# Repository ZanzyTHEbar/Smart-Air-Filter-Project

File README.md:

# :man_technologist:

## Smart Air Filter Project Controller

## :cat: Air Filter Project for Cats and Home :cat2:

This repo is dedicated to the **Smart Air Filter Project**, an automated system for purifying cat litter air.

# WHAT IS THIS PROJECT

This project is dedicated to designing PCB and programming files to bring Smart Air Filtering to the DIY community. Using water as the filtration medium, no need for expensive consumable filters. 

# Things to Do

**__Hardware__**

- [x] Formulate project as PlatformIO
- [x] Integrate the PCB schematic layout
- [x] Integrate a BOM parts list for PCB
- [x] Integrate a Pick and Place file
- [ ] Integrate Panelised PCB gerber files
- [ ] Integrate SPI SRAM chip instead of SD Card
- [ ] Integrate speakers for audio feedback

**__Software__**

- [x] Implement proper memory management
- [ ] Implement proper error handling&logging
- [ ] Implement proper documentation
- [ ] Implement proper debugging for testing
- [ ] Add custom sounds for speakers
- [x] implement code as proper custom library
- [ ] implement dual core system archtecture
        --> Networking on one core and Application code on the other (esp32 is dual core)

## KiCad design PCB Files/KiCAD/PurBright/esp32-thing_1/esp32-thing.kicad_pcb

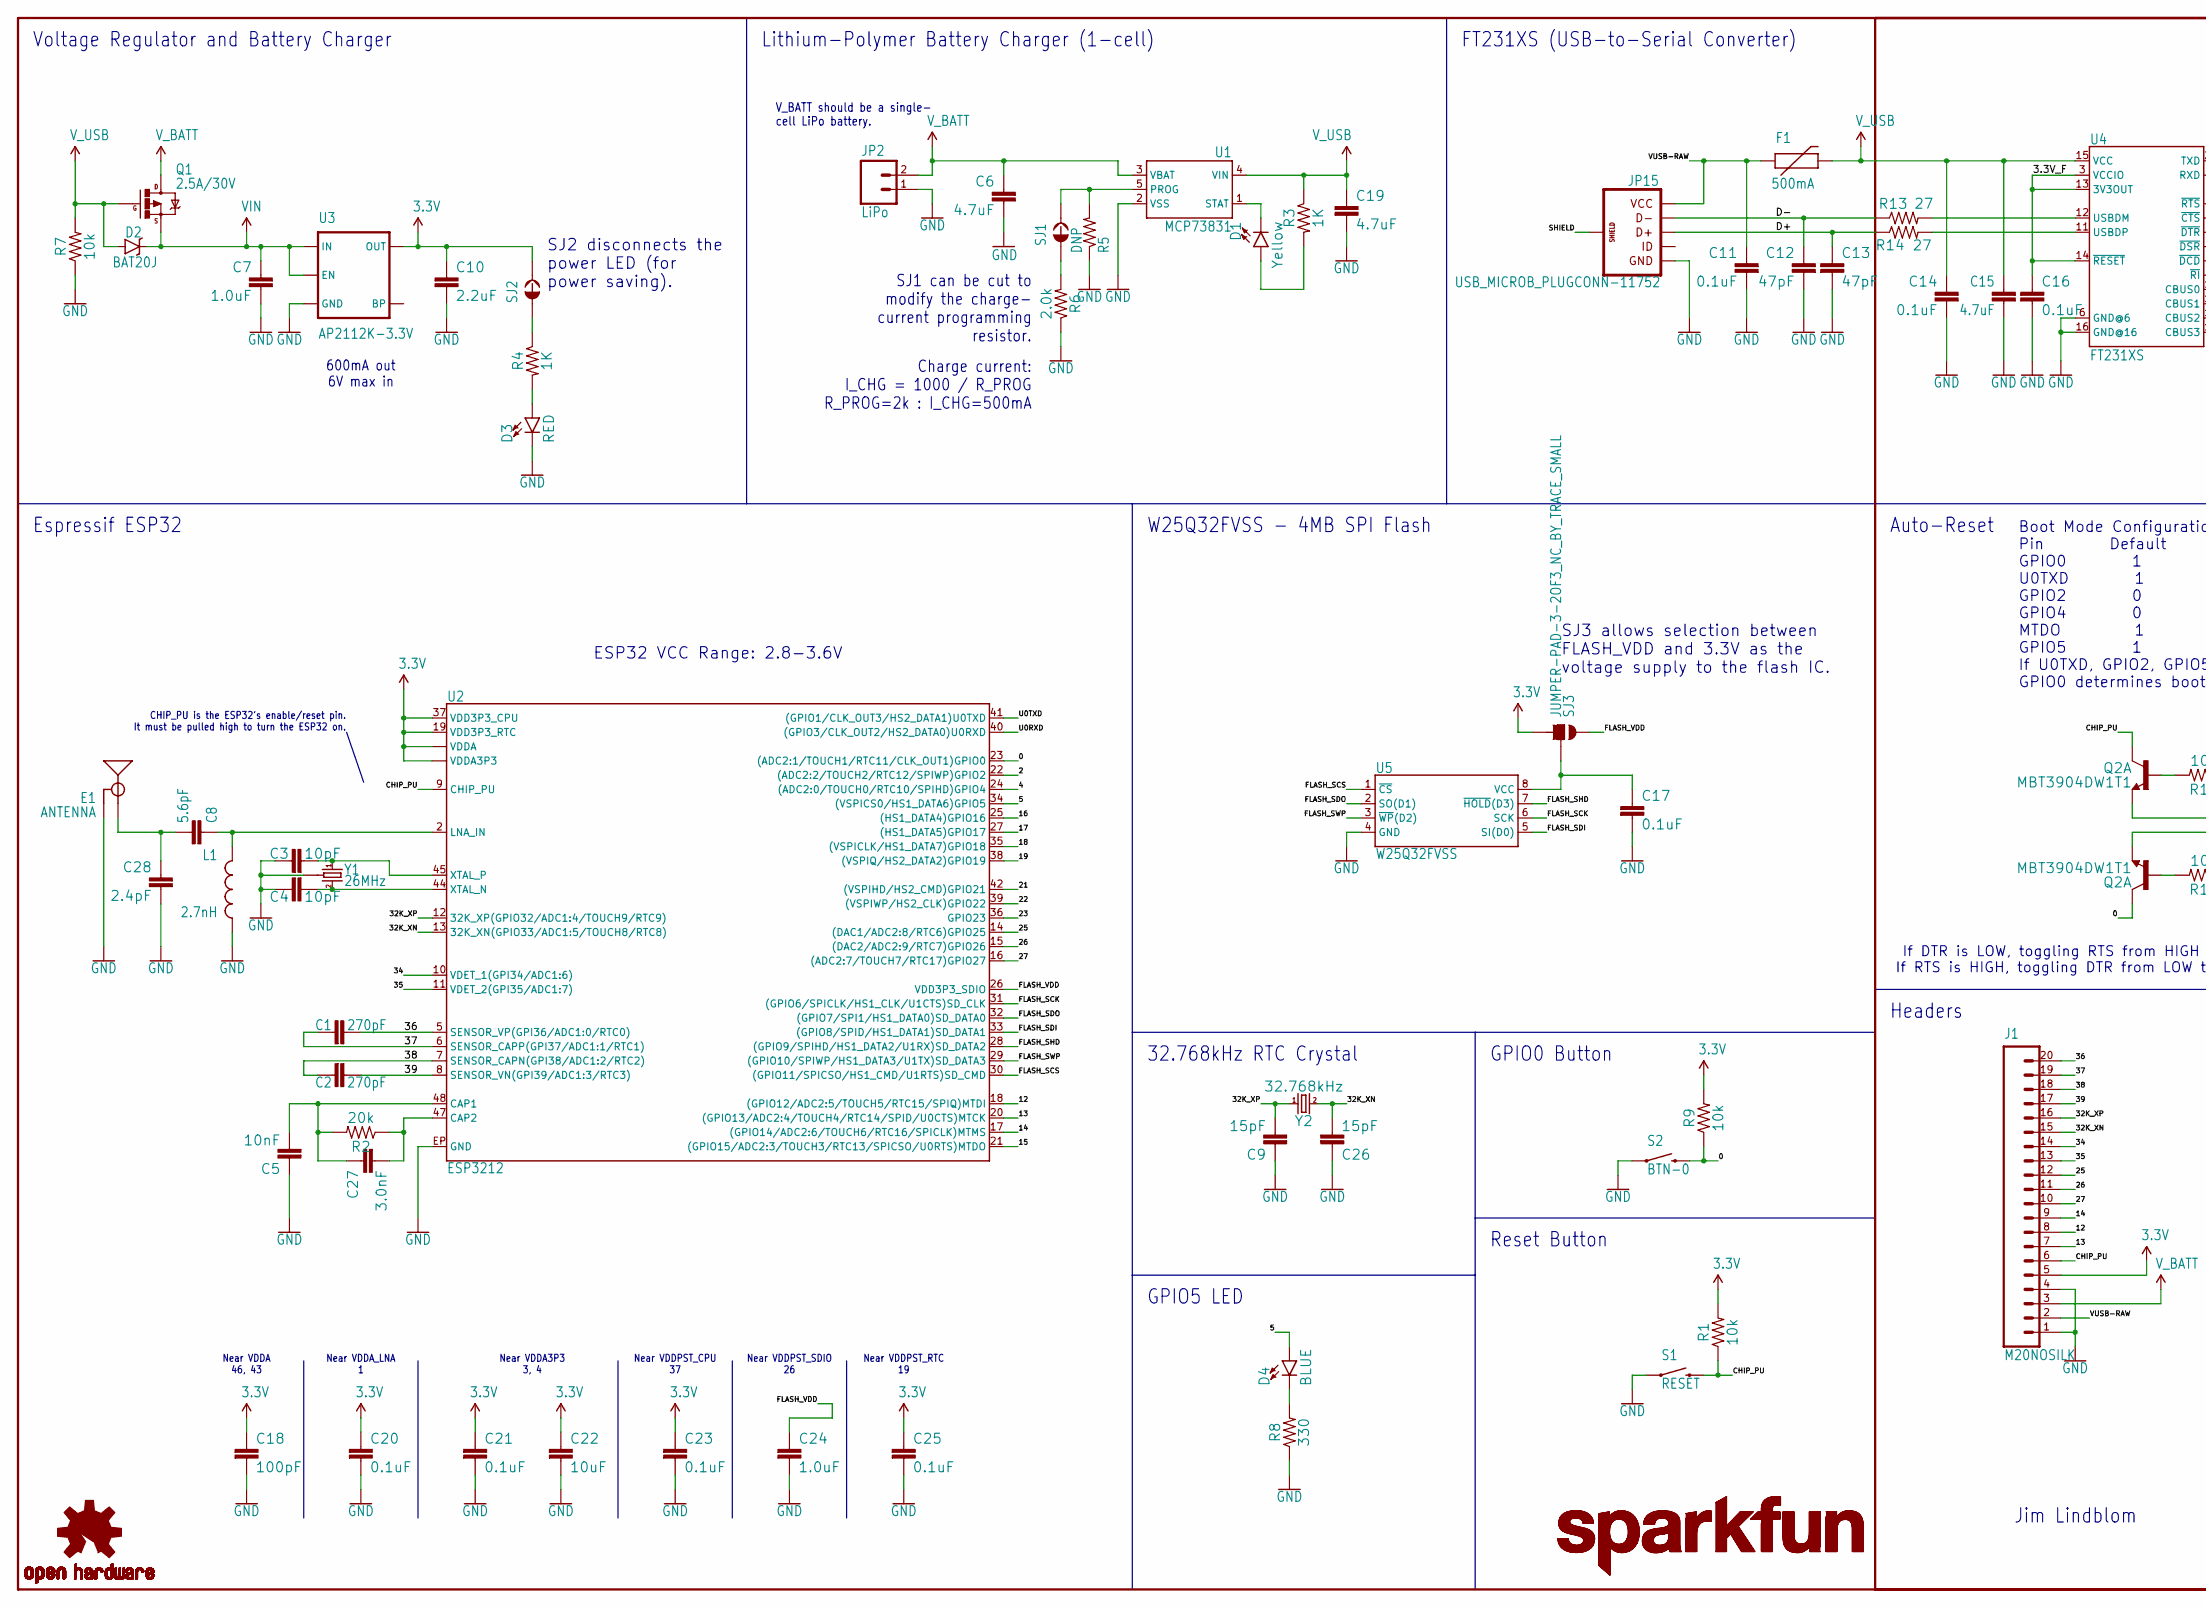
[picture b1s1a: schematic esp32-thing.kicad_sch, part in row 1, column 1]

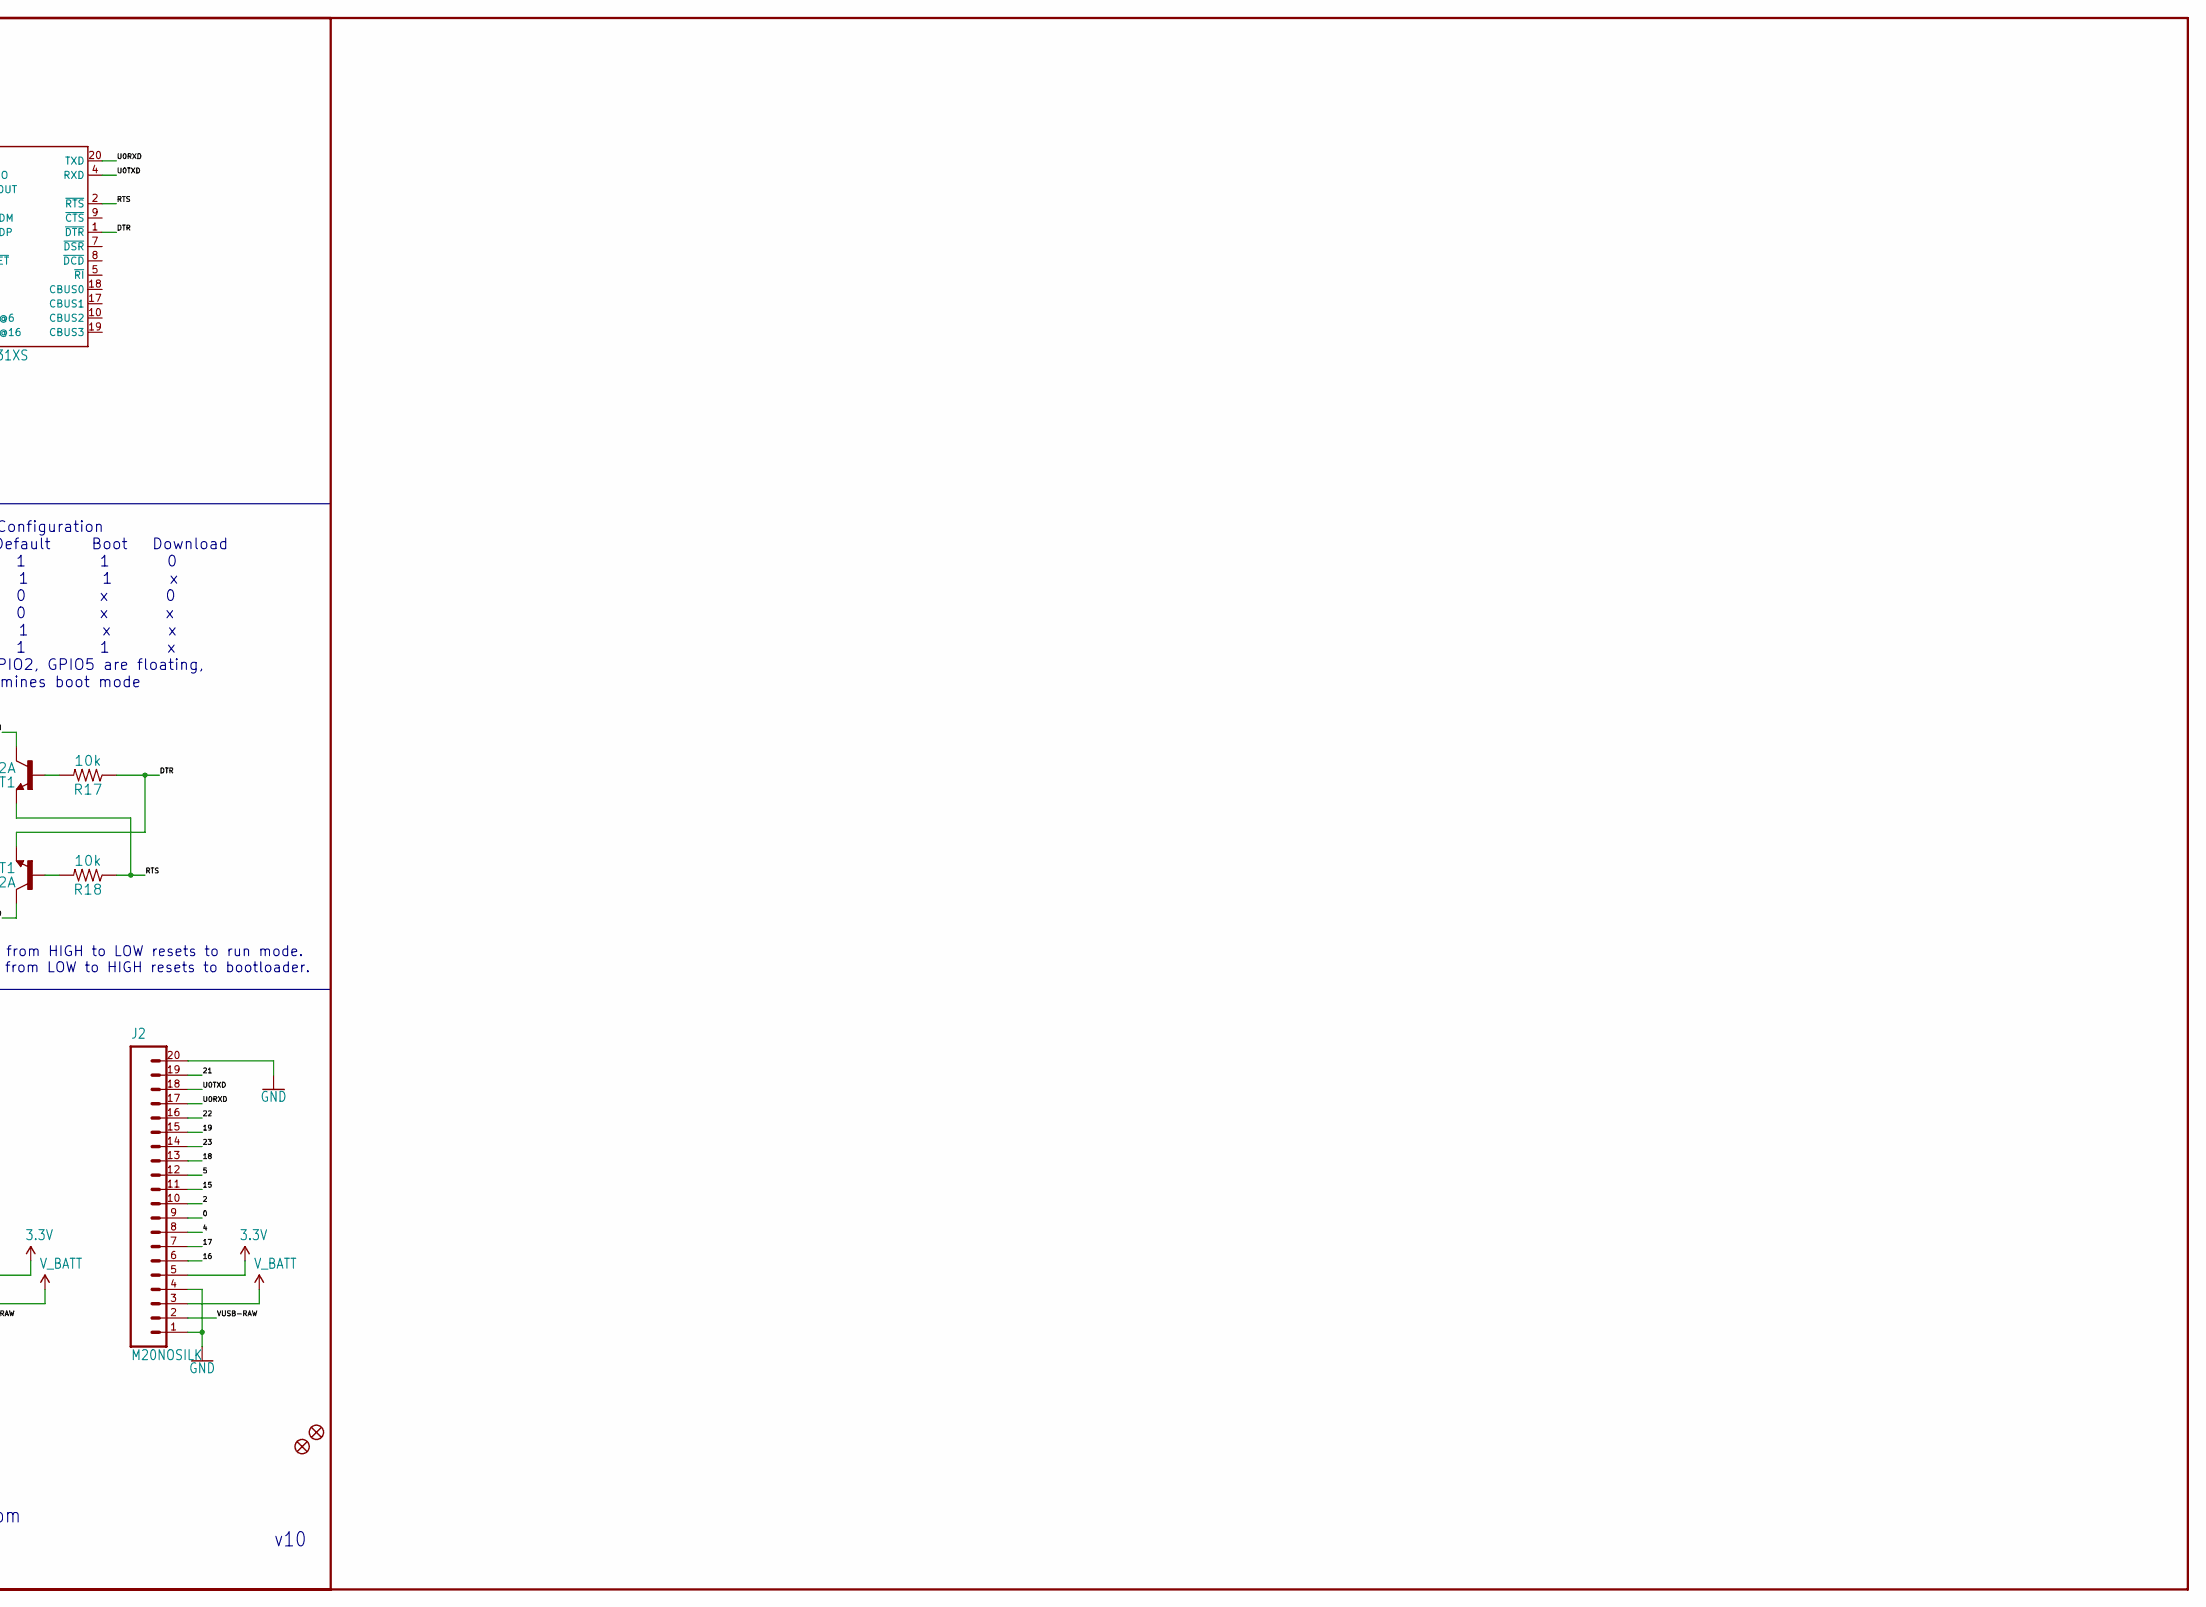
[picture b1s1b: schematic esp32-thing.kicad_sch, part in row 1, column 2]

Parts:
C1, C2: 270pF; 0603
C3, C4: 10pF; 0603
C5: 10nF; 0603
C6, C19: 4.7uF; 0603
C7: 1.0uF; 0805
C8: CAP-12456; 0603
C9, C26: 15pF; 0603
C10: 2.2uF; 0603
C11, C14, C16, C17, C20, C21, C23, C25: 0.1uF; 0603
C12, C13: 47pF; 0603
C15: 4.7uF; 0603-CAP
C18: 100pF; 0603
C22: 10uF; 0603
C24: 1.0uF; 0603
C27: 3.0nF; 0603
C28: 2.4pF; 0603
D1: Yellow; LED-0603
D2: BAT20J; SOD-323
D3: RED; LED-0603
D4: BLUE; LED-0603
E1: ANTENNA; TRACE_ANTENNA_2.4GHZ_25.7MM_TUNED
F1: 500mA; PTC-1206
FD1, FD2: FIDUCIALUFIDUCIAL; MICRO-FIDUCIAL
FRAME1: FRAME-LEDGER; CREATIVE_COMMONS
J1, J2: M20NOSILK; 1X20_NOSILK
JP2: LiPo; JST-2-PTH
JP15: USB_MICROB_PLUGCONN-11752; USB-B-MICRO-SMD_V03
L1: NDUC-08762; 0603
LOGO1, LOGO3: SFE_LOGO_NAME.2_INCH; SFE_LOGO_NAME_.2
LOGO2: OSHW-LOGOMINI; OSHW-LOGO-MINI
Q1: 2.5A/30V; SOT23-3
Q2: MBT3904DW1T1; SC70-6
R1, R7, R9, R17, R18: 10k; 0603
R2: 20k; 0603
R3, R4: 1K; 0603
R5: DNP; 1_6W-RES
R6: 2.0k; 0603
R8: 330; 0603
R13, R14: 27; 0603
S1: RESET; TACTILE_SWITCH_SMD_4.6X2.8MM
S2: BTN-0; TACTILE_SWITCH_SMD_4.6X2.8MM
SJ1, SJ2: JUMPER-PAD-2-NC_BY_TRACE; PAD-JUMPER-2-NC_BY_TRACE_YES_SILK
SJ3: JUMPER-PAD-3-2OF3_NC_BY_TRACE_SMALL; PAD-JUMPER-3-2OF3_NC_BY_TRACE_YES_SILK_FULL_BOX
U1: MCP73831; SOT23-5
U2: ESP3212; QFN48-0.4MM
U3: VREG-12457; SOT23-5
U4: FT231XS; SSOP20_L
U5: W25Q32FVSS; SOIC-8
Y1: XTAL-12454; CRYSTAL-SMD-3.2X2.5
Y2: 32.768kHz; CRYSTAL-SMD-3.2X1.5MM

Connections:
2: J2.10, U2.22 ((ADC2:2/TOUCH2/RTC12/SPIWP)GPIO2)
3.3V: C10.1, C18.1, C20.1, C21.1, C22.1, C23.1, C25.1, J1.5, J2.5, R1.2, R9.2, SJ2.2, SJ3.3, U2.1 (VDDA), U2.3 (VDDA3P3), U2.4 (VDDA3P3), U2.19 (VDD3P3_RTC), U2.37 (VDD3P3_CPU), U2.43 (VDDA), U2.46 (VDDA), U3.5 (OUT)
3.3V_F: C16.1, U4.3 (VCCIO), U4.13 (3V3OUT), U4.14 (~RESET)
4: J2.8, U2.24 ((ADC2:0/TOUCH0/RTC10/SPIHD)GPIO4)
5: D4.A, J2.12, U2.34 ((VSPICS0/HS1_DATA6)GPIO5)
12: J1.8, U2.18 ((GPIO12/ADC2:5/TOUCH5/RTC15/SPIQ)MTDI)
13: J1.7, U2.20 ((GPIO13/ADC2:4/TOUCH4/RTC14/SPID/U0CTS)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)
14: J1.9, U2.17 ((GPIO14/ADC2:6/TOUCH6/RTC16/SPICLK)MTMS)
15: J2.11, U2.21 ((GPIO15/ADC2:3/TOUCH3/RTC13/SPICSO/U0RT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)
16: J2.6, U2.25 ((HS1_DATA4)GPIO16)
17: J2.7, U2.27 ((HS1_DATA5)GPIO17)
18: J2.13, U2.35 ((VSPICLK/HS1_DATA7)GPIO18)
19: J2.15, U2.38 ((VSPIQ/HS2_DATA2)GPIO19)
21: J2.19, U2.42 ((VSPIHD/HS2_CMD)GPIO21)
22: J2.16, U2.39 ((VSPIWP/HS2_CLK)GPIO22)
23: J2.14, U2.36 (GPIO23)
25: J1.12, U2.14 ((DAC1/ADC2:8/RTC6)GPIO25)
26: J1.11, U2.15 ((DAC2/ADC2:9/RTC7)GPIO26)
27: J1.10, U2.16 ((ADC2:7/TOUCH7/RTC17)GPIO27)
32K_XN: C26.2, J1.15, U2.13 (32K_XN(GPIO33/ADC1:5/TOUCH8/RTC8)), Y2.P$2 (2)
32K_XP: C9.2, J1.16, U2.12 (32K_XP(GPIO32/ADC1:4/TOUCH9/RTC9)), Y2.P$1 (1)
34: J1.14, U2.10 (VDET_1(GPI34/ADC1:6))
35: J1.13, U2.11 (VDET_2(GPI35/ADC1:7))
36: C1.2, J1.20, U2.5 (SENSOR_VP(GPI36/ADC1:0/RTC0))
37: C1.1, J1.19, U2.6 (SENSOR_CAPP(GPI37/ADC1:1/RTC1))
38: C2.1, J1.18, U2.7 (SENSOR_CAPN(GPI38/ADC1:2/RTC2))
39: C2.2, J1.17, U2.8 (SENSOR_VN(GPI39/ADC1:3/RTC3))
CAP_10N: C5.2, C27.1, R2.2, U2.48 (CAP1)
D+: C13.1, JP15.D+, R14.1
D-: C12.1, JP15.D-, R13.1
FLASH_SCK: U2.31 ((GPIO6/SPICLK/HS1_CLK/U1CTS)SD_CLK), U5.6 (SCK)
FLASH_SCS: U2.30 ((GPIO11/SPICSO/HS1_CMD/U1RTS)SD_CMD), U5.1 (~CS)
FLASH_SDI: U2.33 ((GPIO8/SPID/HS1_DATA1)SD_DATA1), U5.5 (SI(D0))
FLASH_SDO: U2.32 ((GPIO7/SPI1/HS1_DATA0)SD_DATA0), U5.2 (SO(D1))
FLASH_SHD: U2.28 ((GPIO9/SPIHD/HS1_DATA2/U1RX)SD_DATA2), U5.7 (~HOLD(D3))
FLASH_SWP: U2.29 ((GPIO10/SPIWP/HS1_DATA3/U1TX)SD_DATA3), U5.3 (~WP(D2))
FLASH_VDD: C24.1, SJ3.1, U2.26 (VDD3P3_SDIO)
GND: C3.1, C4.1, C5.1, C6.2, C7.2, C9.1, C10.2, C11.2, C12.2, C13.2, C14.2, C15.2, C16.2, C17.2, C18.2, C19.2, C20.2, C21.2, C22.2, C23.2, C24.2, C25.2, C26.1, C28.2, D3.C, E1.GND, E1.GND2 (GND), J1.1, J1.4, J2.1, J2.4, J2.20, JP2.1, JP15.GND, L1.2, R5.1, R6.1, R7.1, R8.1, S1.1, S1.2 (1), S2.1, S2.2 (1), U1.2 (VSS), U2.EP (GND), U3.2 (GND), U4.6 (GND@6), U4.16 (GND@16), U5.4 (GND), Y1.2 (GND), Y1.4 (GND)
LNA_IN: C8.1, L1.1, U2.2 (LNA_IN)
unnamed: D4.C, R8.2
unnamed: D3.A, R4.2
unnamed: R4.1, SJ2.1
unnamed: C27.2, R2.1, U2.47 (CAP2)
unnamed: R13.2, U4.12 (USBDM)
unnamed: R14.2, U4.11 (USBDP)
unnamed: D1.C, U1.1 (STAT)
unnamed: C17.1, SJ3.2, U5.8 (VCC)
unnamed: C3.2, U2.45 (XTAL_P), Y1.1
unnamed: R5.2, SJ1.2, U1.5 (PROG)
unnamed: C4.2, U2.44 (XTAL_N), Y1.3 (2)
unnamed: R6.2, SJ1.1
unnamed: D1.A, R3.2
SHIELD: JP15.SHIELD1 (SHIELD), JP15.SHIELD2 (SHIELD), JP15.SHIELD3 (SHIELD)
TRACE_ANT: C8.2, C28.1, E1.ANT (SIGNAL)
U0RXD: J2.17, U2.40 ((GPIO3/CLK_OUT2/HS2_DATA0)U0RXD), U4.20 (TXD)
U0TXD: J2.18, U2.41 ((GPIO1/CLK_OUT3/HS2_DATA1)U0TXD), U4.4 (RXD)
VIN: C7.1, D2.C, Q1.2 (S), U3.1 (IN), U3.3 (EN)
VUSB-RAW: C11.1, F1.1, J1.2, J2.2, JP15.VBUS (VCC)
V_BATT: C6.1, J1.3, J2.3, JP2.2, Q1.3 (D), U1.3 (VBAT)
V_USB: C14.1, C15.1, C19.1, D2.A, F1.2, Q1.1 (G), R3.1, R7.2, U1.4 (VIN), U4.15 (VCC)

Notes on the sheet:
Near VDDA 46, 43
Near VDDPST_CPU 37
CHIP_PU is the ESP32's enable/reset pin. It must be pulled high to turn the ESP32 on.
Charge current: I_CHG = 1000 / R_PROG R_PROG=2k : I_CHG=500mA
Boot Mode Configuration Pin Default Boot Download GPIO0 1 1 0 U0TXD 1 1 x GPIO2 0 x 0 GPIO4 0 x x MTDO 1 x x GPIO5 1 1 x If U0TXD, GPIO2, GPIO5 are floating, GPIO0 determines boot mode
If DTR is LOW, toggling RTS from HIGH to LOW resets to run mode. If RTS is HIGH, toggling DTR from LOW to HIGH resets to bootloader.
32.768kHz RTC Crystal
Lithium-Polymer Battery Charger (1-cell)
Headers
SJ1 can be cut to modify the charge- current programming resistor.
Voltage Regulator and Battery Charger
FT231XS (USB-to-Serial Converter)
v10
ESP32 VCC Range: 2.8-3.6V
600mA out 6V max in
V_BATT should be a single- cell LiPo battery.
Espressif ESP32
Jim Lindblom
W25Q32FVSS - 4MB SPI Flash
SJ2 disconnects the power LED (for power saving).
Reset Button
Near VDDPST_SDIO 26
Near VDDA_LNA 1
Auto-Reset
Near VDDPST_RTC 19
SJ3 allows selection between FLASH_VDD and 3.3V as the voltage supply to the flash IC.
GPIO5 LED
Near VDDA3P3 3, 4
GPIO0 Button

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
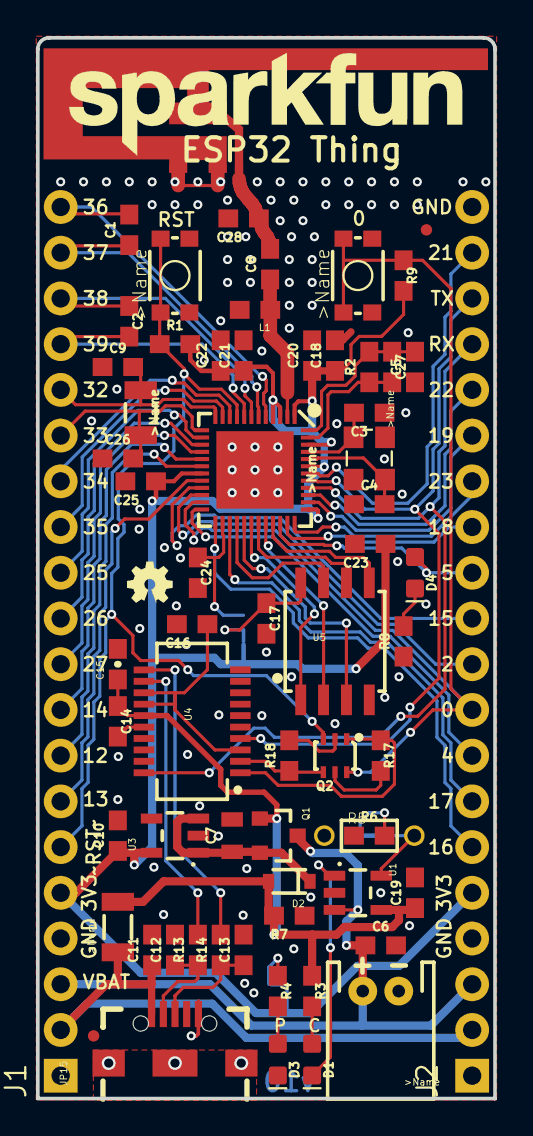
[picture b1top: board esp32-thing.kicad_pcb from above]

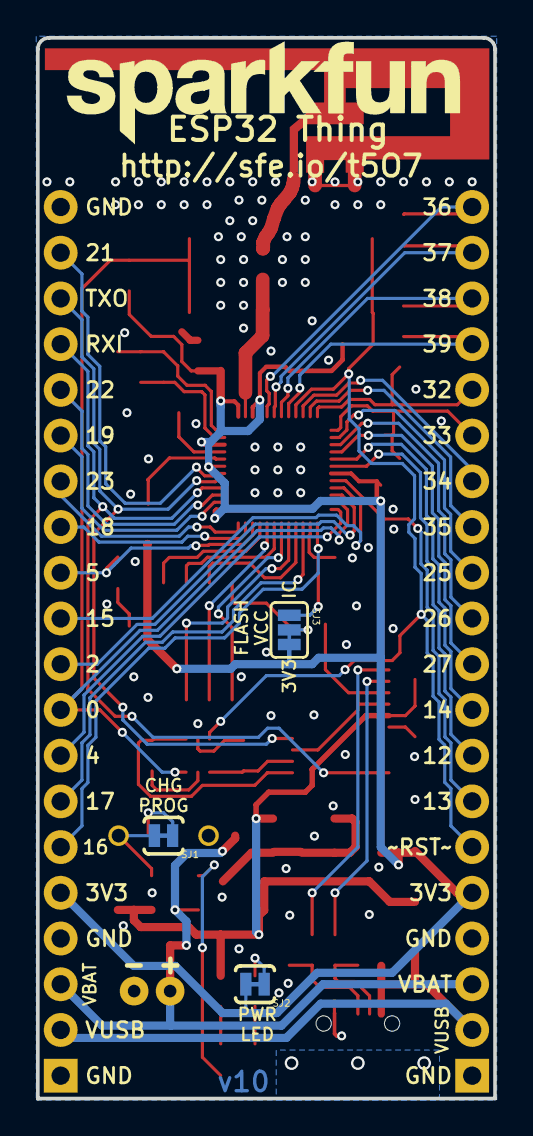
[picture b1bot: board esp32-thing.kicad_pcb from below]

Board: 2 copper layers, 25.4 x 58.9 mm, 72 parts (4 on the bottom side), 66 nets.

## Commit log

2022-02-17 update code
    Full Refactor of project
2022-06-05 update - fully functional
2022-06-07 update - begin added MQTT support
2022-06-07 update
    - Fix buttons class with state management enum
2022-06-07 update - implement Home Assistant Support
2022-06-10 update
    - Beging adding namespace and statemachine logic
2022-06-10 adding namespaces

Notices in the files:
PCB Files/KiCAD/PurBright/esp32-thing_1/esp32-thing.kicad_sch:
https://creativecommons.org/licenses/by-sa/4.0
Released under the Creative Commons
parts and their libraries:
Released under the Creative Commons Attribution Share-Alike 4.0 License
